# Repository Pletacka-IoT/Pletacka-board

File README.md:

# Pletacka-boad

## [Version 2.0](Pletacka-board-v2.0/README.md)

# [All photos](./Pletacka-board-v2.0/media/README.md)

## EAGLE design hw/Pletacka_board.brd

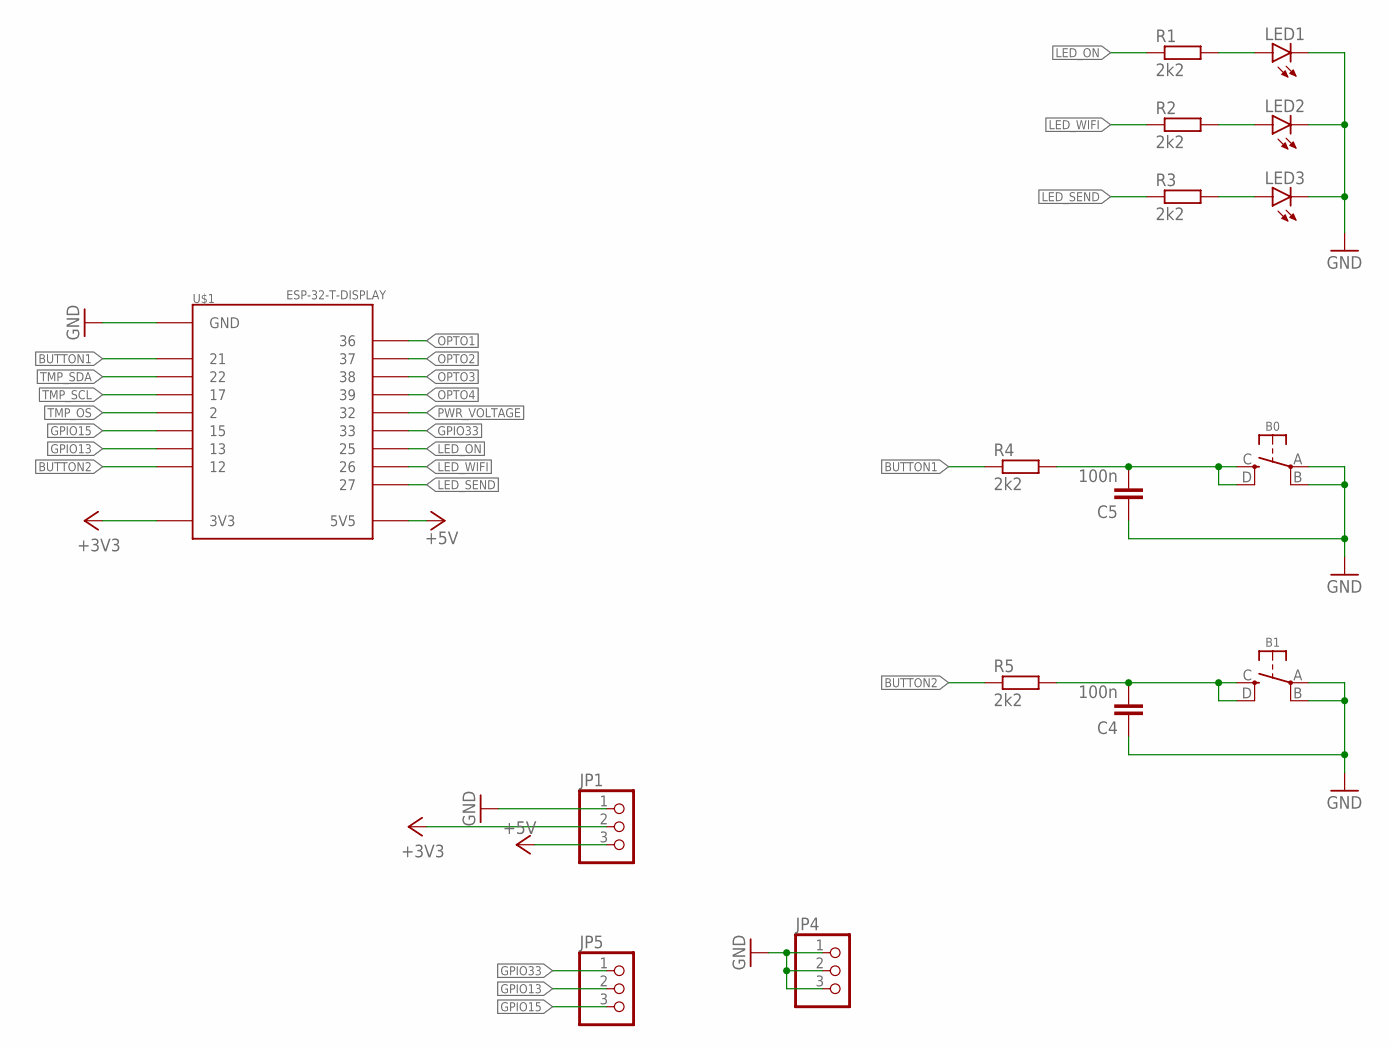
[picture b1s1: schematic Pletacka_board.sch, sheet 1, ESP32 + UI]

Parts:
B0: ENTER; TS-1187A; LCSC_ID C318888
B1: B1; TS-1187A; LCSC_ID C318888
C4, C5: 100n; C0603; LCSC_ID C14663
JP1, JP4, JP5: PINHD-1X3; 1X03
LED1, LED2, LED3: LEDCHIPLED_0603; CHIPLED_0603; LCSC_ID C2286
R1, R2, R3, R4, R5: 2k2; R0603; LCSC_ID C4190
U$1: ESP-32-T-DISPLAY; ESP32-T-DISPLAY

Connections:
+3V3: JP1.2, U$1.3V3, U$1.3V3-2 (3V3); also elsewhere on the board
+5V: JP1.3, U$1.5V (5V5); also elsewhere on the board
BUTTON1: R4.1, U$1.21
BUTTON2: R5.1, U$1.12
GND: B0.A, B0.B (P1), B1.A, B1.B (P1), C4.1, C5.1, JP1.1, JP4.1, JP4.2, JP4.3, LED1.C, LED2.C, LED3.C, U$1.G-1 (GND), U$1.G-2 (GND), U$1.G-3 (GND), U$1.G-4 (GND), U$1.G-5 (GND); also elsewhere on the board
GPIO13: JP5.2, U$1.13
GPIO15: JP5.3, U$1.15
GPIO33: JP5.1, U$1.33
LED_ON: R1.1, U$1.25
LED_SEND: R3.1, U$1.27
LED_WIFI: R2.1, U$1.26
unnamed: LED1.A, R1.2
unnamed: LED2.A, R2.2
unnamed: B0.C (S), B0.D (S1), C5.2, R4.2
unnamed: B1.C (S), B1.D (S1), C4.2, R5.2
unnamed: LED3.A, R3.2
OPTO1: U$1.36; also elsewhere on the board
OPTO2: U$1.37; also elsewhere on the board
OPTO3: U$1.38; also elsewhere on the board
OPTO4: U$1.39; also elsewhere on the board
PWR_VOLTAGE: U$1.32; also elsewhere on the board
TMP_OS: U$1.2; also elsewhere on the board
TMP_SCL: U$1.17; also elsewhere on the board
TMP_SDA: U$1.22; also elsewhere on the board

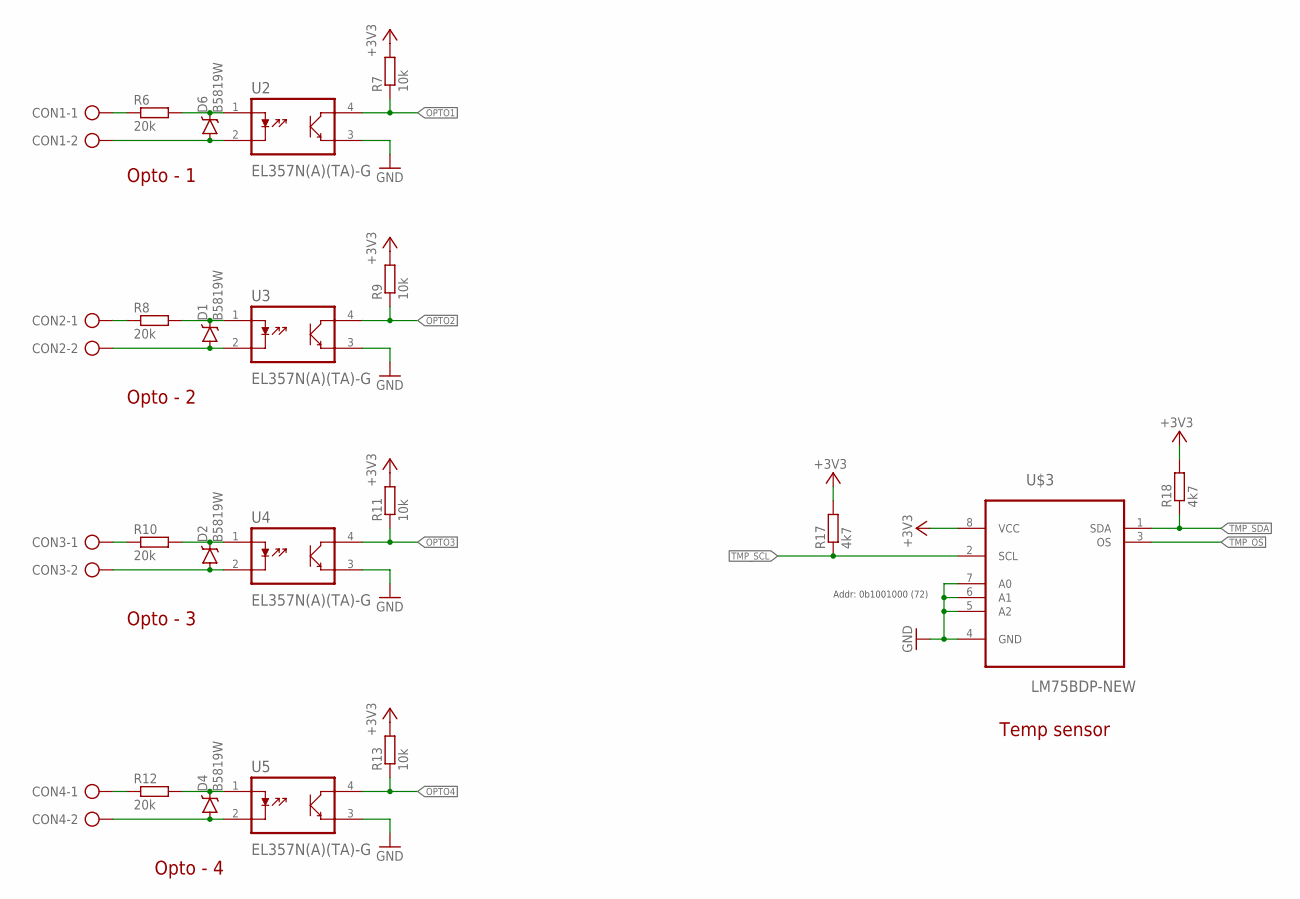
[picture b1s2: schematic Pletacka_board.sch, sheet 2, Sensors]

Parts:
CON1, CON2, CON3, CON4: AK500/2
D1, D2, D4, D6: B5819W; SOD-123; LCSC_ID C8598
R6, R8, R10, R12: 20k; R0603; LCSC_ID C4184
R7, R9, R11, R13: 10k; R0603; LCSC_ID C25804
R17, R18: 4k7; R0603; LCSC_ID C23162
U2, U3, U4, U5: EL357N(A)(TA)-G; SOP254P700X200-4N; LCSC_ID C6649
U$3: LM75BDP-NEW; SOT505-1; LCSC_ID C33099

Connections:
+3V3: R7.2, R9.2, R11.2, R13.2, R17.2, R18.2, U$3.8 (VCC); also elsewhere on the board
GND: U2.3 (E), U3.3 (E), U4.3 (E), U5.3 (E), U$3.4 (GND), U$3.5 (A2), U$3.6 (A1), U$3.7 (A0); also elsewhere on the board
unnamed: CON1.1, R6.1
unnamed: CON1.2, D6.A, U2.2 (K)
unnamed: D6.C, R6.2, U2.1 (A)
unnamed: CON2.1, R8.1
unnamed: CON2.2, D1.A, U3.2 (K)
unnamed: D1.C, R8.2, U3.1 (A)
unnamed: CON3.1, R10.1
unnamed: CON3.2, D2.A, U4.2 (K)
unnamed: D2.C, R10.2, U4.1 (A)
unnamed: CON4.1, R12.1
unnamed: CON4.2, D4.A, U5.2 (K)
unnamed: D4.C, R12.2, U5.1 (A)
OPTO1: R7.1, U2.4 (C); also elsewhere on the board
OPTO2: R9.1, U3.4 (C); also elsewhere on the board
OPTO3: R11.1, U4.4 (C); also elsewhere on the board
OPTO4: R13.1, U5.4 (C); also elsewhere on the board
TMP_OS: U$3.3 (OS); also elsewhere on the board
TMP_SCL: R17.1, U$3.2 (SCL); also elsewhere on the board
TMP_SDA: R18.1, U$3.1 (SDA); also elsewhere on the board

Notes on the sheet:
Opto - 1
Opto - 2
Opto - 3
Opto - 4
Temp sensor
Addr: 0b1001000 (72)

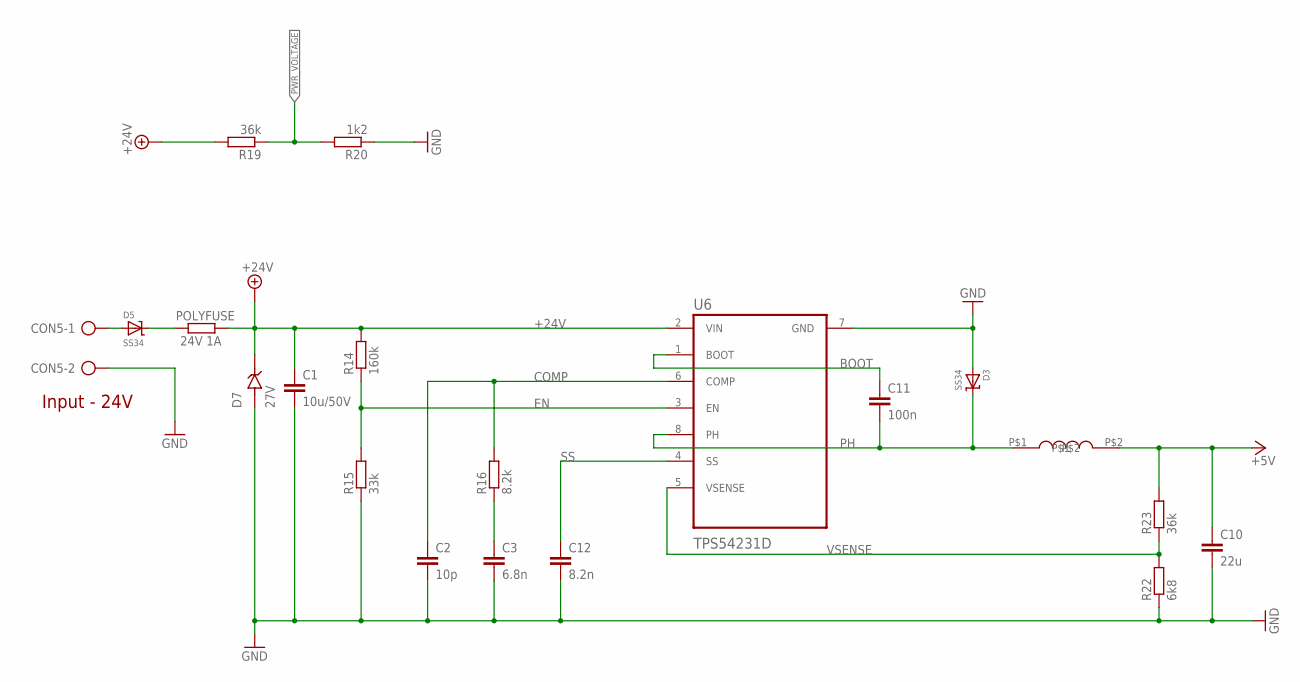
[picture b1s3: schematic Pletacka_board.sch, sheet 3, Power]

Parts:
C1: 10u/50V; C1206; LCSC_ID C13585
C2: 10p; C0603; LCSC_ID C1634
C3: 6.8n; C0603; LCSC_ID C1631
C10: 22u; C0805; LCSC_ID C45783
C11: 100n; C0603; LCSC_ID C14663
C12: 8.2n; C0603; LCSC_ID C27920
CON5: AK500/2
D3, D5: SS34; SMA; LCSC_ID C8678
D7: 27V; DIOM5436X247N; LCSC_ID C49827
POLYFUSE: 24V 1A; R1206; LCSC_ID C70076
R14: 160k; R0603; LCSC_ID C22813
R15: 33k; R0603; LCSC_ID C4216
R16: 8.2k; R0603; LCSC_ID C25981
R19, R23: 36k; R0603; LCSC_ID C23147
R20: 1k2; R0603; LCSC_ID C22765
R22: 6k8; R0603; LCSC_ID C23212
U6: TPS54231D; SOIC127P599X175-8N; LCSC_ID C28023
U$2: SWRB1204S; LCSC_ID C169399

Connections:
+5V: C10.1, R23.2, U$2.P$2; also elsewhere on the board
+24V: C1.1, D7.C (K), POLYFUSE.1, R14.2, R19.2, U6.2 (VIN)
BOOT: C11.1, U6.1 (BOOT)
COMP: C2.1, R16.2, U6.6 (COMP)
EN: R14.1, R15.2, U6.3 (EN)
GND: C1.2, C2.2, C3.2, C10.2, C12.2, CON5.2, D3.A, D7.A, R15.1, R20.1, R22.1, U6.7 (GND); also elsewhere on the board
unnamed: CON5.1, D5.A
unnamed: D5.C, POLYFUSE.2
unnamed: C3.1, R16.1
PH: C11.2, D3.C, U6.8 (PH), U$2.P$1
PWR_VOLTAGE: R19.1, R20.2; also elsewhere on the board
SS: C12.1, U6.4 (SS)
VSENSE: R22.2, R23.1, U6.5 (VSENSE)

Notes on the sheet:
Input - 24V

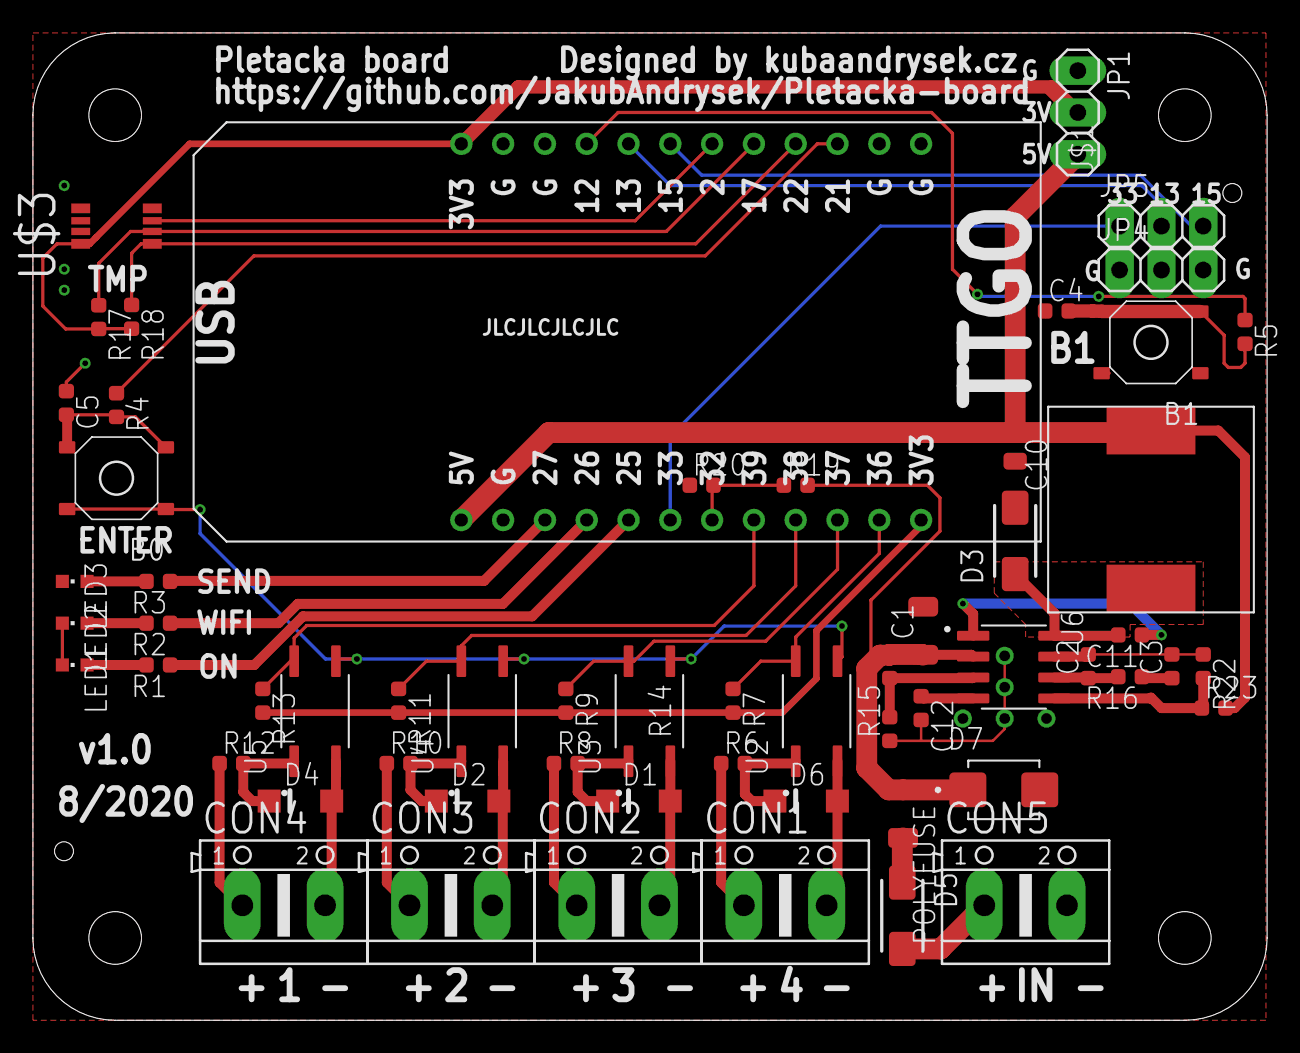
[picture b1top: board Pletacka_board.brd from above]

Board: 2 copper layers, 75.0 x 60.0 mm, 59 parts (0 on the bottom side), 46 nets.

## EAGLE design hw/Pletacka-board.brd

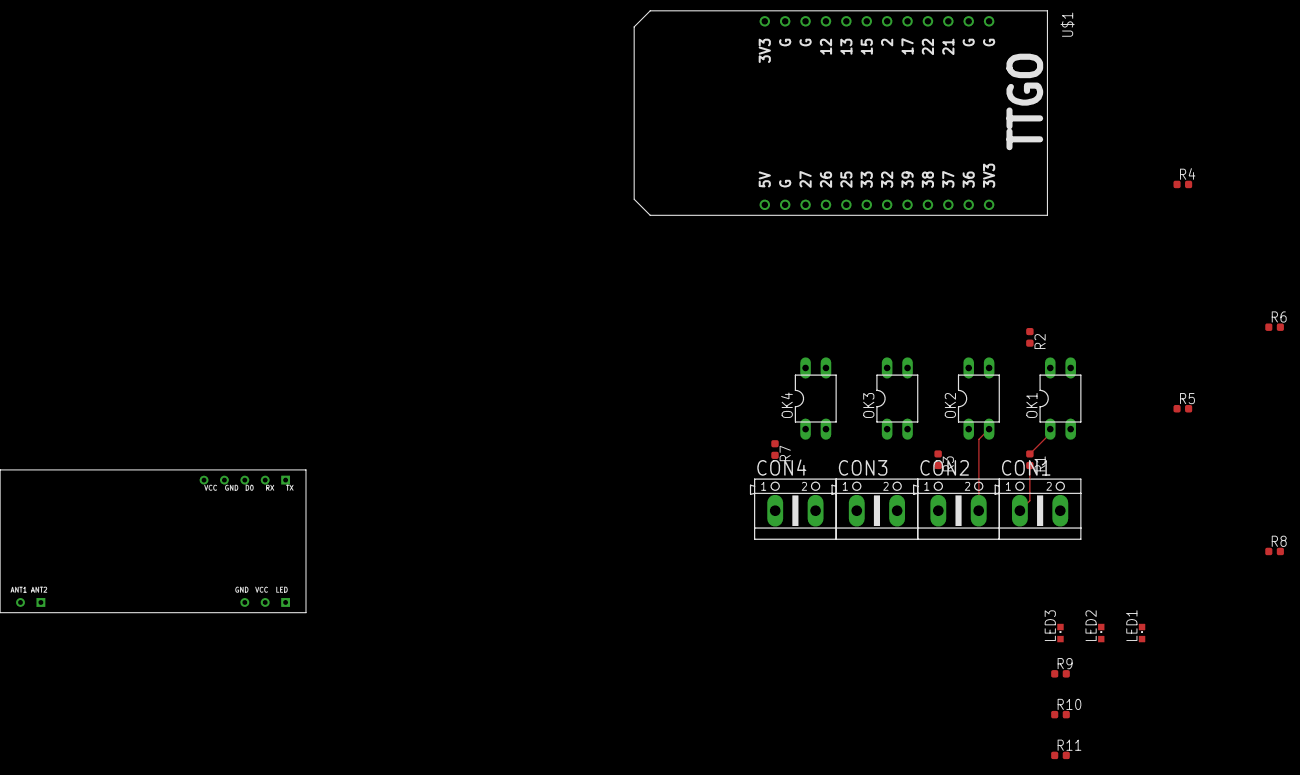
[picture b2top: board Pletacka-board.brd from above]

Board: 2 copper layers, 24 parts (0 on the bottom side), 24 nets.

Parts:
CON1, CON2, CON3, CON4: AK500/2
LED1, LED2, LED3: CHIPLED_0603
OK1, OK2, OK3, OK4: PC817; DIL04
R1, R3, R5, R7: 1K; R0603
R2, R4, R6, R8: 4K7; R0603
R9, R10, R11: 330R; R0603
RDM1: RDM6300
U$1: ESP-32-T-DISPLAY; ESP32-T-DISPLAY

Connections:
+3V3: R2.1, R4.1, R6.1, R8.1, U$1.3V3
+5V: RDM1.VCC, U$1.5V
GND: LED1.C, LED2.C, LED3.C, OK1.3, OK2.3, OK3.3, OK4.3, RDM1.GND, U$1.G-1
LED_POWER: R9.2, U$1.21
LED_SEND: R11.2, U$1.17
LED_WIFI: R10.2, U$1.22
unnamed: OK1.1, R1.1
unnamed: CON2.2, OK2.2
unnamed: CON1.1, R1.2
unnamed: OK2.1, R3.1
unnamed: CON2.1, R3.2
unnamed: CON3.2, OK3.2
unnamed: OK3.1, R5.1
unnamed: CON3.1, R5.2
unnamed: OK4.1, R7.1
unnamed: CON4.1, R7.2
unnamed: LED1.A, R9.1
unnamed: LED2.A, R10.1
unnamed: LED3.A, R11.1
OPTO1: OK1.4, R2.2, U$1.36
OPTO2: OK2.4, R4.2, U$1.37
OPTO3: OK3.4, R6.2, U$1.38
OPTO4: OK4.4, R8.2, U$1.39
RFID: RDM1.RX, U$1.32

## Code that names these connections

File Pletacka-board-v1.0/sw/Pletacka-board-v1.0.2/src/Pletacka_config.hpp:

#pragma once

const int LED_SEND  = 27;
const int LED_WIFI = 26;
const int LED_ON = 25;
const int OP_1_FINISH = 39;
const int OP_2_STOP = 38;
const int OP_3 = 37;
const int OP_4 = 36;
const int BTN_ENTER = 21;
const int BTN_B1 = 12;
const int BTN_UP = 0;
const int BTN_DOWN = 35;
const int TMP_SDA = 22;
const int TMP_SCL = 17;
const int TMP_OS = 2;
const int PWR_VOLTAGE = 32;
const int GPIO_13 = 13;
const int GPIO_15 = 15;
const int GPIO_33 = 33;

const int EEPROM_SIZE = 50;
const int EEPROM_SNUMBER_A = 5;

struct PletackaConfig
{
	PletackaConfig()
		: sensorNumber(1)
		, serverUrl("")
		, serverUrlBackup("")
		, wifiName("")
		, wifiPassword("")
		, wifiChenel(1)
		, debugOn(false)
		, udpIP("192.168.0.112")
		, udpPort(2727)
		{

	}

	int sensorNumber;   //Sensor number
	String serverUrl; 	//Server URL address
	String serverUrlBackup; 	//Server URL address
	String wifiName;    //WiFi name
	String wifiPassword;//WiFi password
	int wifiChenel;     //WiFi chanel
	bool debugOn;	//Startup into debug mode - Serial Debug
	String udpIP;
	int udpPort;

};

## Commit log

2020-06-18 Start creating board
2020-06-18 Add buttons and LEDs
2020-06-18 Add temperature sensor
2020-06-18 Remove old files
2020-06-19 Start routing
2020-06-19 One more time from start
2020-06-19 Start new project
2020-06-19 Add LEDs, RFID, Temp sen.
2020-06-19 Add Buttons + optocouplers
2020-07-23 Start power management
2020-07-27 cesgaw
2020-08-09 Route power supply
2020-08-09 Finish first routing
2020-08-09 Add 2 pinheads
2020-08-09 Fix Cednik's issues
2020-08-10 Start fixing
2020-08-10 Fix all atributes (fix #12)
2020-08-10 Change octocoupler resistor to 20k (close #2)
2020-08-10 Change step-down voltage (close #4)
2020-08-10 Change package of capacitor to 0805 (close #3)
2020-08-10 Edit buttons lables (close #16)
2020-08-10 Fix power supply routing (close #5 and close #6)
2020-08-10 Rename POWER to ON (close #7)
2020-08-10 Fix ON button schema name
2020-08-10 Add PS reverse polarity & over. pr. (close #8)
2020-08-11 Improve schema for step-down input
    - improve readability of over-voltage protection in schema
    - fix some minor issues (LCSC_IDs, ...)
2020-08-11 Fix Beware of tombstoning (close #9)
2020-08-11 Add JLCPCB order n. and tooling holes (close #11)
2020-08-11 Add pull-up resistors on I2C (close #14)
2020-08-11 Add input power voltage mesurement
2020-08-11 Move voltage mesurement resistors
2020-08-12 Update resistor R15
2020-08-12 Update Polyfuse atribute
2020-08-12 Fix ports rotation
2020-10-16 Start new version 2.0 in Kicad
2020-10-16 Create ESP32-TTGO library
2020-10-16 Add gitignore
2020-10-16 Add files
2020-10-16 Add octocoupler library
2020-10-17 Add libraries
2020-10-17 Add connectors
2020-10-17 Update some packages, add 3D models
2020-10-18 Update some packages
2020-10-18 Routing schema
2020-10-18 Routing board
2020-10-18 Add Kicad project file
2020-10-18 Update improve schema and broke board
2020-10-18 Remove blank sheets
2020-10-19 New routing of board
2020-10-19 Change buttons and fill ground
2020-10-19 Repair files problem
2020-10-19 Add Kuba Logo
2020-10-19 Fix small issues
2020-10-19 Change Inductor
2020-10-19 Testin fabrication export
2020-10-21 Finish board
2020-10-21 Add pictures, update redme
2020-10-24 Change file structure & add old version 1.0
2020-10-25 Add software v1
2020-10-25 Change file name - software v1.0
2020-10-25 Add sw v2
2020-10-25 Update to new version of display library
2020-10-25 Remove buttons - chage board
2020-10-25 Add export to gitignore
2020-10-25 Add new version 1.0.1
2020-10-25 Fix multiple files include
2020-10-25 Run GridUI from main.c
2020-10-25 Move GridUI to Pletacka
2020-10-26 Add sensor number change by gridUI
2020-10-26 Testing v1.0.2
2020-10-26 Add UI - Protocol
2020-10-26 Repair main
2020-10-26 Fix Board tester
2020-10-26 Improveing GridUI View
2020-10-28 Add few versions
2020-10-29 Add stable version
2020-11-13 New stable version
2020-11-15 Fix Layoyt sending
2020-11-15 Fix Config file name
2020-12-12 Add cover, SW-v2.0
2020-12-12 New set ID button, change behavior
2020-12-15 Nice schema
2021-02-27 Add v2.0.2 (fix display, add speed)
2022-10-15 Update gitignore

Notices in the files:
parts and their libraries:
Copyright (C) Vlada 2004-2005
